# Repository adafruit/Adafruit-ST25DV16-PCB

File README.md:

## Adafruit Adafruit ST25DV16K I2C RFID EEPROM Breakout - STEMMA QT / Qwiic PCB

<a href="http://www.adafruit.com/products/4701"><br/>
Click here to purchase one from the Adafruit shop</a>

PCB files for the Adafruit Adafruit ST25DV16K I2C RFID EEPROM Breakout - STEMMA QT / Qwiic. 

Format is EagleCAD schematic and board layout
* https://www.adafruit.com/product/4701

### Description

This RFID tag is really unique: it works with mobile phones just like other RFID tags, but you can reprogram it over I2C. The tag shows up as an ISO/IEC 15693 (13.56MHz) chip which is readable by phones and tablets. This could be interesting in situations where you want a  tag that can be re-written dynamically when connected to a controller. For example, we did a test where we had a microcontroller write different URLs a few seconds apart, and the mobile phone detected the different URLs one after the other.

### License

Adafruit invests time and resources providing this open source design, please support Adafruit and open-source hardware by purchasing products from [Adafruit](https://www.adafruit.com)!

Designed by Kattni Rembor for Adafruit Industries.

Creative Commons Attribution/Share-Alike, all text above must be included in any redistribution. 
See license.txt for additional details.

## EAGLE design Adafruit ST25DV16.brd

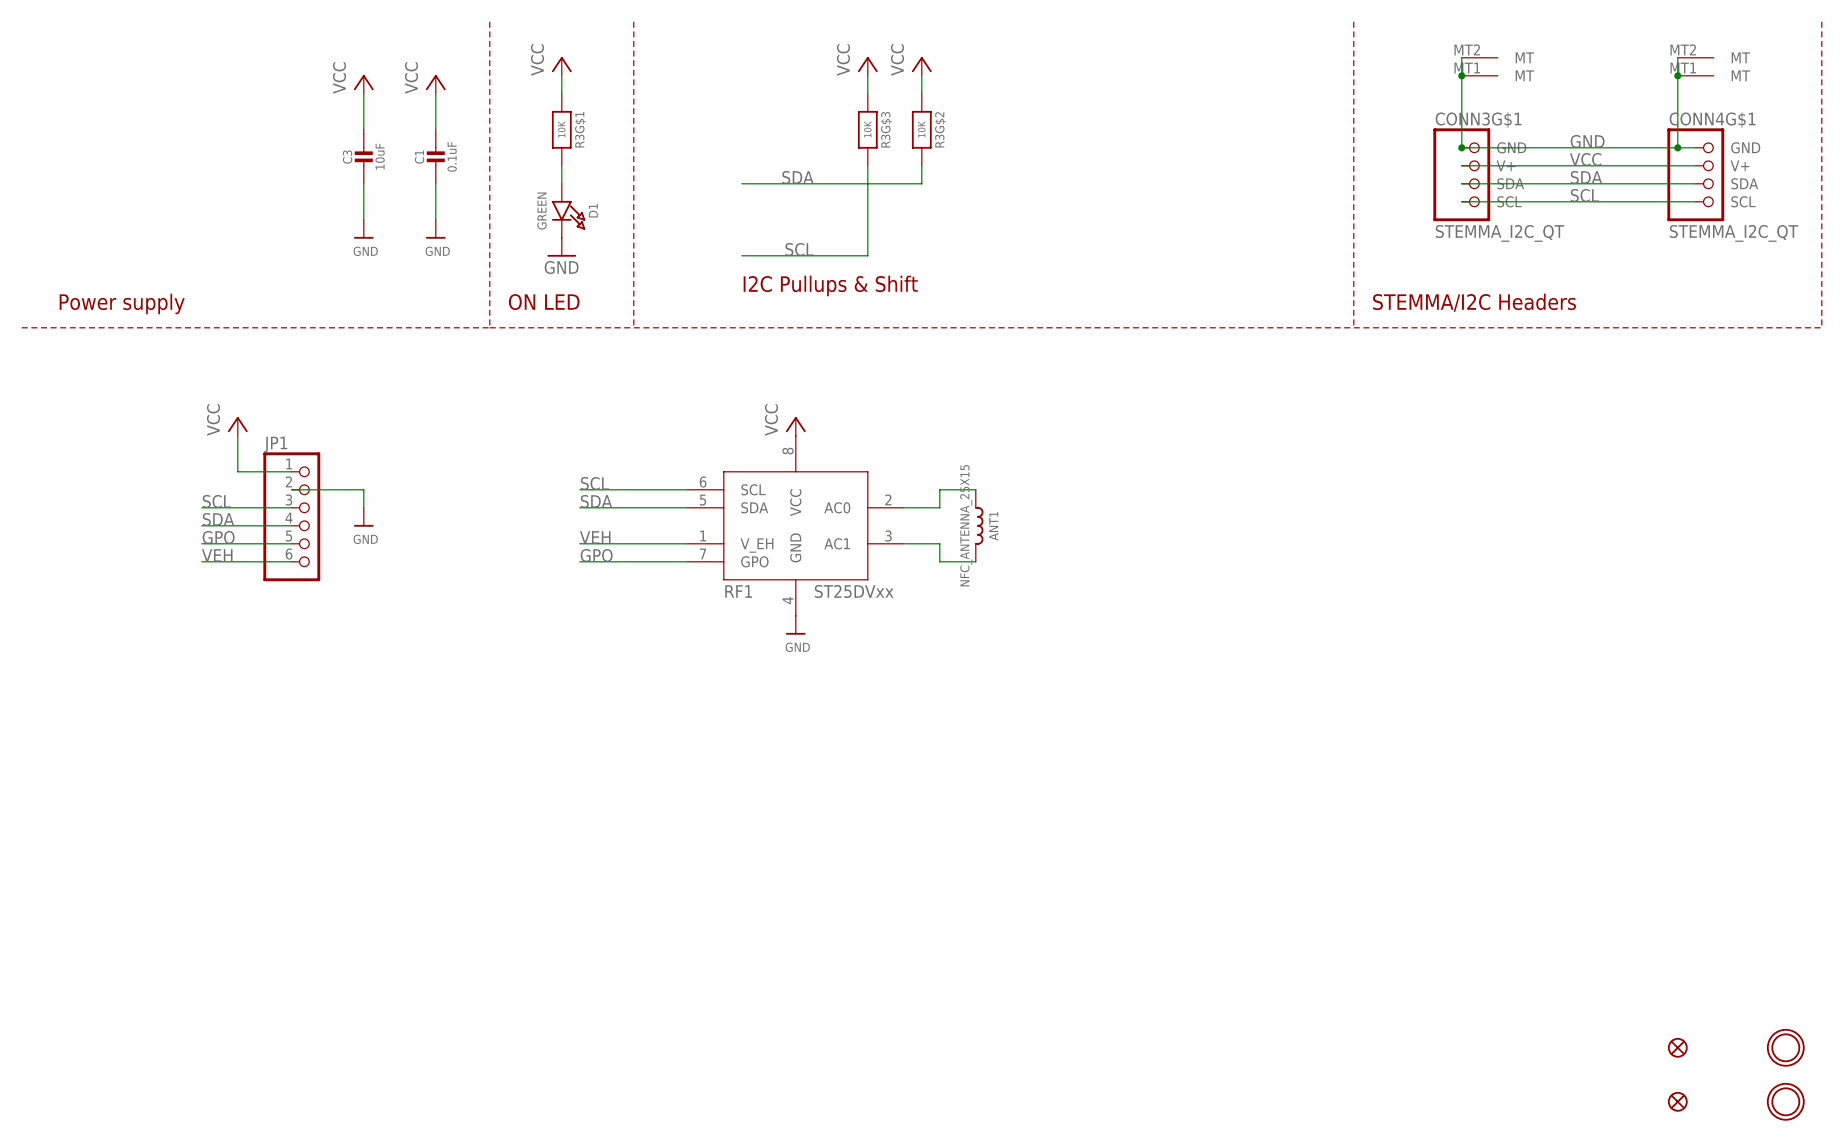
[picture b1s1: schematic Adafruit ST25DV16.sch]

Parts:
ANT1: NFC_ANTENNA_25X15; NFCANT_25X15
C1: 0.1uF; 0603-NO
C3: 10uF; 0805-NO
CONN3, CONN4: STEMMA_I2C_QT; JST_SH4
D1: GREEN; CHIPLED_0603_NOOUTLINE
FID3, FID4: FIDUCIAL_1MM
JP1: HEADER-1X670MIL; 1X06_ROUND_70
R3: 10K; RESPACK_4X0603
RF1: ST25DVXX_TSSOP; TSSOP8-4.4MM
U$19, U$21: MOUNTINGHOLE2.5; MOUNTINGHOLE_2.5_PLATED

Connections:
GND: C1.2, C3.2, CONN3.1 (GND), CONN3.MT1 (MT), CONN3.MT2 (MT), CONN4.1 (GND), CONN4.MT1 (MT), CONN4.MT2 (MT), D1.C, JP1.2, RF1.4 (GND)
GPO: JP1.5, RF1.7 (GPO)
unnamed: D1.A, R3.8 (2)
unnamed: ANT1.P$2 (2), RF1.2 (AC0)
unnamed: ANT1.P$1 (1), RF1.3 (AC1)
SCL: CONN3.4 (SCL), CONN4.4 (SCL), JP1.3, R3.6 (2), RF1.6 (SCL)
SDA: CONN3.3 (SDA), CONN4.3 (SDA), JP1.4, R3.7 (2), RF1.5 (SDA)
VCC: C1.1, C3.1, CONN3.2 (V+), CONN4.2 (V+), JP1.1, R3.1, R3.2 (1), R3.3 (1), RF1.8 (VCC)
VEH: JP1.6, RF1.1 (V_EH)

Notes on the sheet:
I2C Pullups & Shift
STEMMA/I2C Headers
ON LED
Power supply

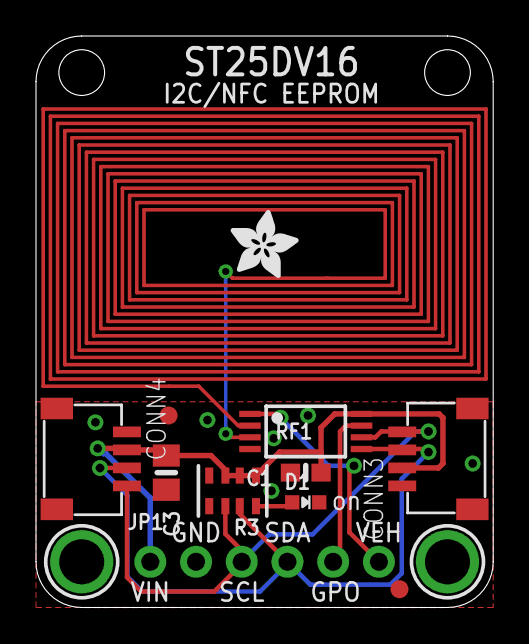
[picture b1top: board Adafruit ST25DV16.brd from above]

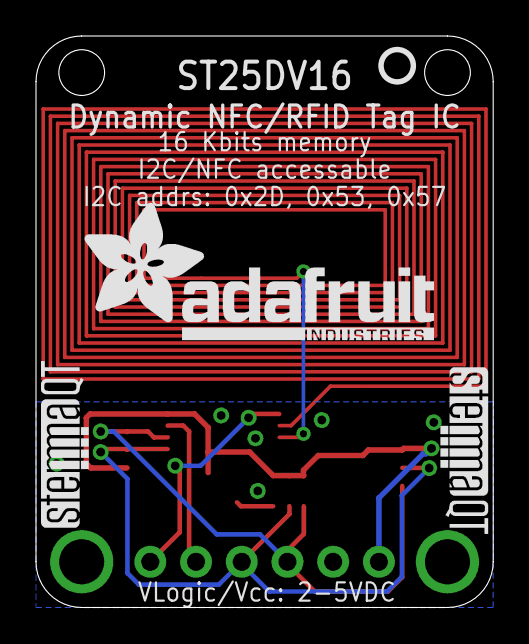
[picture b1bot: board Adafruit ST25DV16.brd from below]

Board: 2 copper layers, 25.4 x 31.8 mm, 18 parts (4 on the bottom side), 9 nets.

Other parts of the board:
U$1: ADAFRUIT_TEXT_20MM
U$22: ADAFRUIT_3.5MM
U$25: PCBFEAT-REV-040
U$30, U$31: STEMMAQT

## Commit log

2020-08-07 Uploading board files

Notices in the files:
parts and their libraries:
microbuilder: This work is placed in the public domain, and may be freely used for commercial and non-commercial work with the following conditions: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
